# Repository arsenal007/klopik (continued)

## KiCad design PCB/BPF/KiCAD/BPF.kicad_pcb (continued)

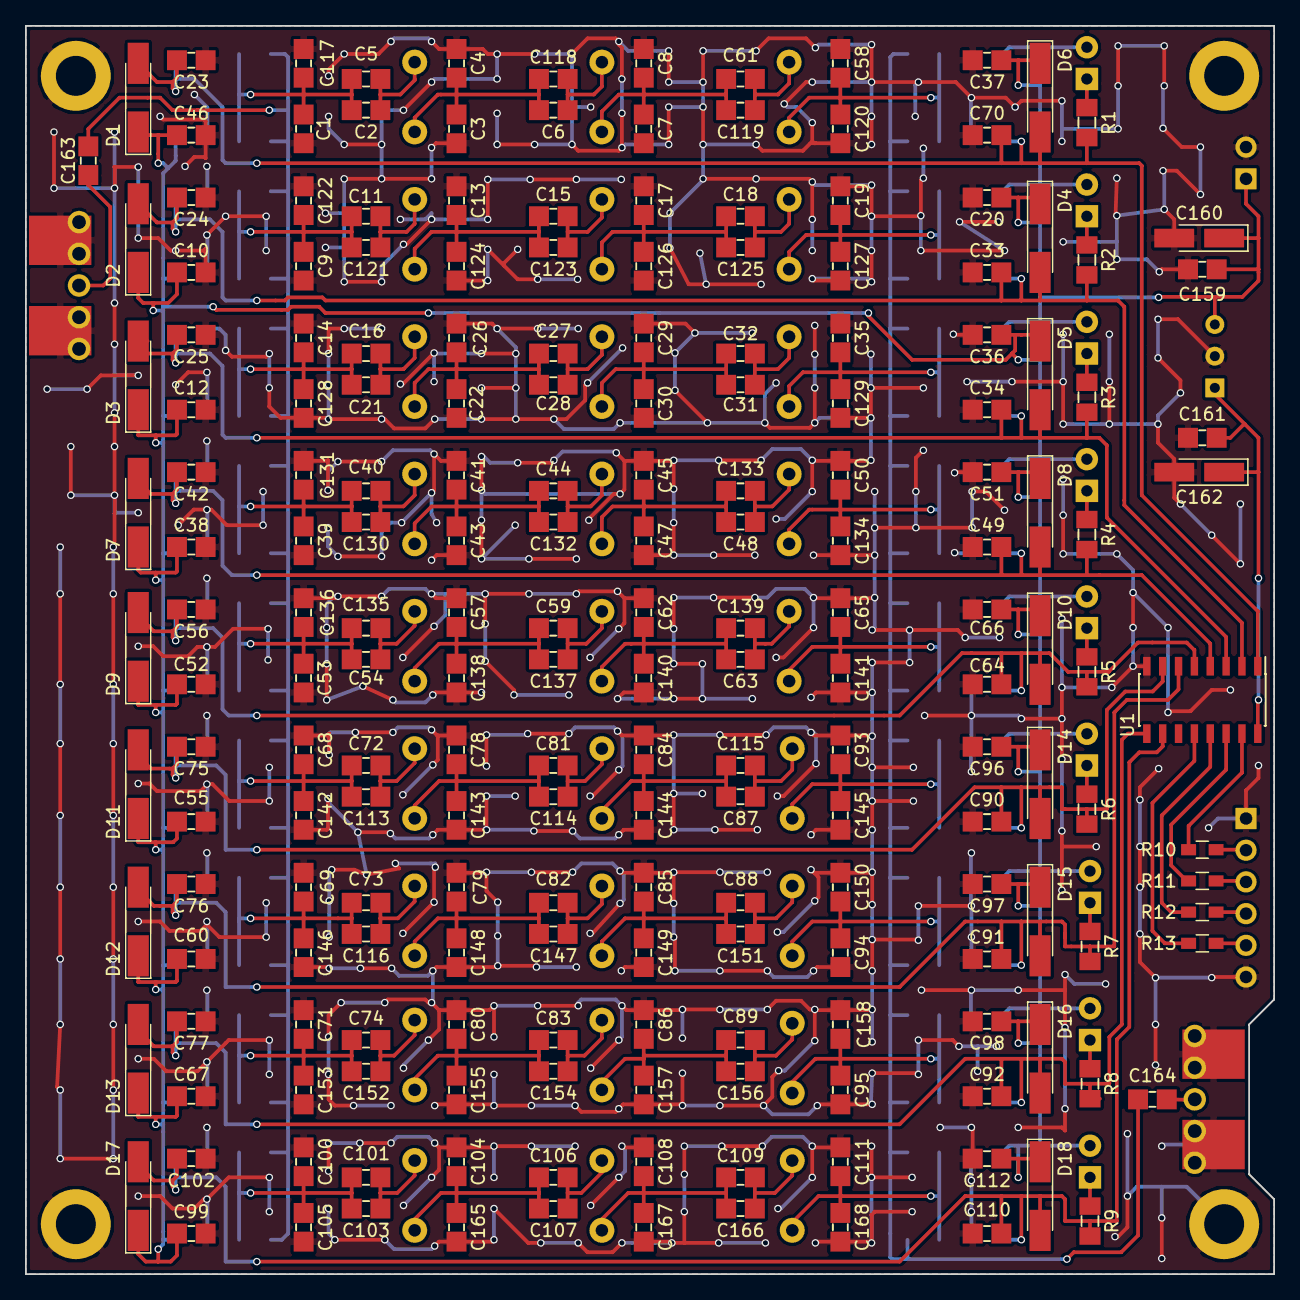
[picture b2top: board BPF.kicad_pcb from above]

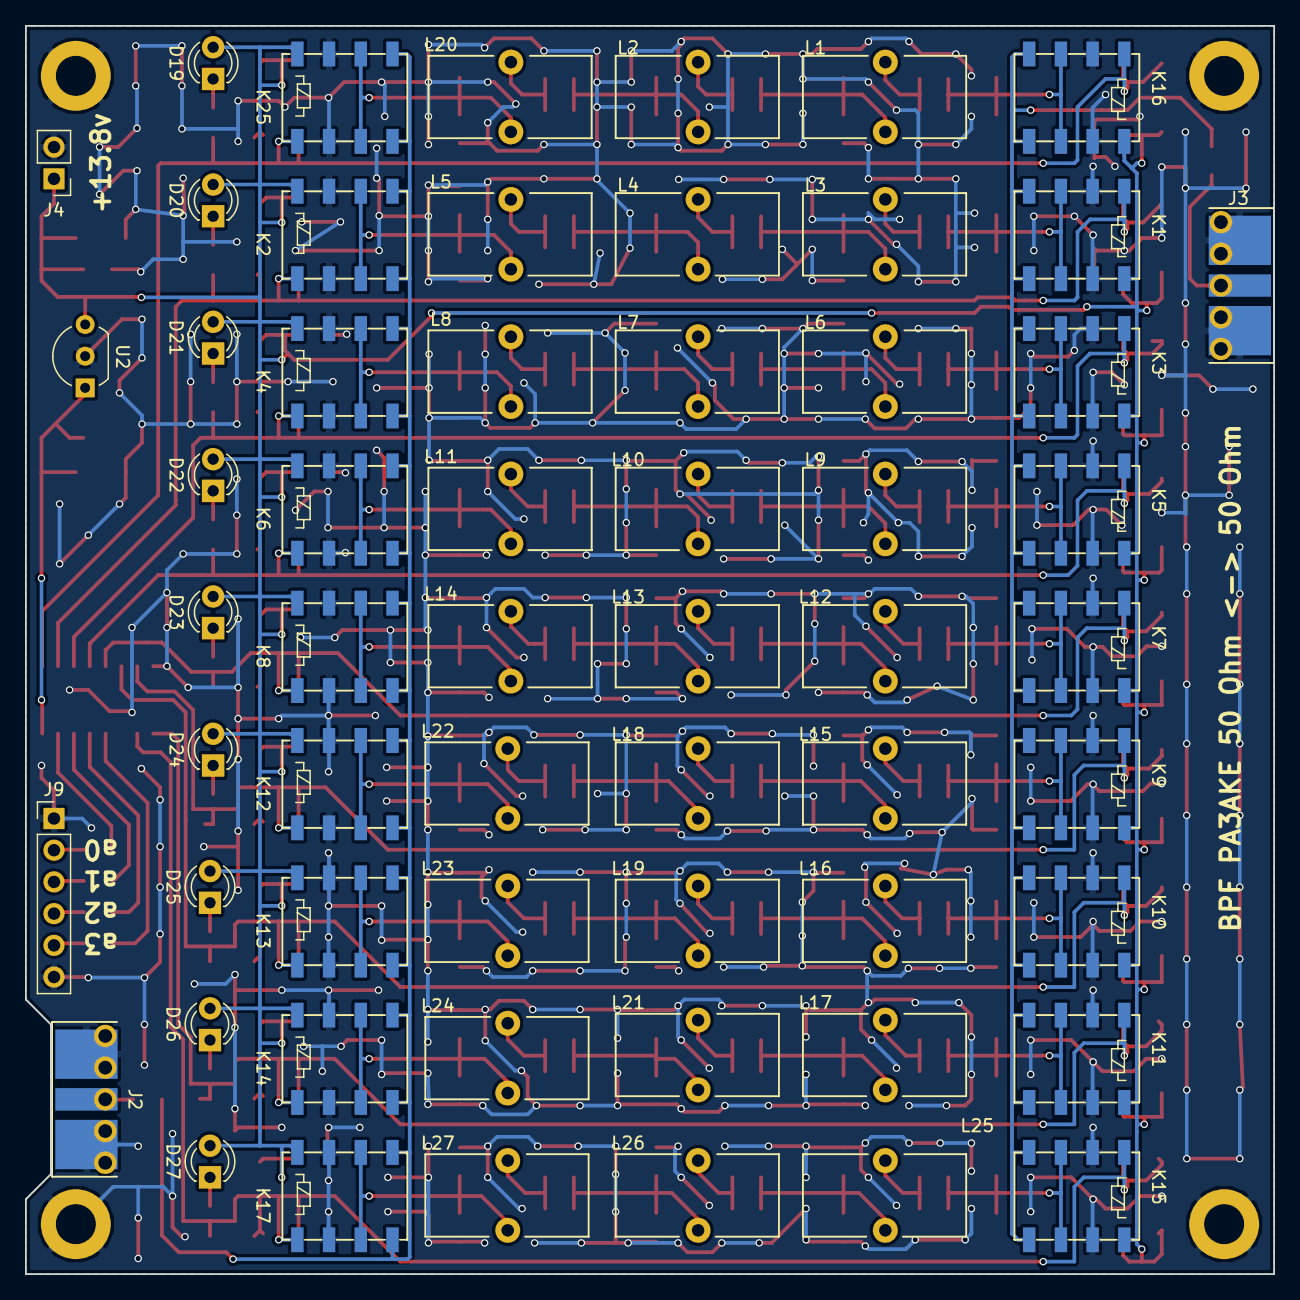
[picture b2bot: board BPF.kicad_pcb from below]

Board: 2 copper layers, 100.0 x 100.0 mm, 263 parts (59 on the bottom side), 96 nets.

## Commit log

2017-12-14 source code for atmega168a
2017-12-14 Add Atmel Studio 7.0 files
2017-12-15 add CMakeList.txt for cmake
2018-04-30 TRX first commit with PCB
2018-05-10 add TRX PCB v1.15
2018-05-19 add BPF PCB
